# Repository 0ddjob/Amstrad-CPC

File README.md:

# Amstrad CPC
Amstrad CPC related projects.

## [Typer-Inner-Checker](/Typer-Inner-Checker)
A simple HTML/web page to aid typing in Locomotive BASIC program listings on a modern computer.  It doesn't run the program, that's for a proper emulator.<br>

This HTML page will:
- Check each line as you type it in
- Colourise/capitalise keywords
- Highlights missing GOTO/GOSUB targets
- Save/load BAS file for resuming where you left off

## [CPC PLUS Floppy Adaptor](/CPC_Plus_Floppy_Adaptor)
An idea to convert the 6128 PLUS model's Centronics floppy connector to a more standard 26-way or 34-way pin header to connect a drive via a ribbon cable.<br>

### Status
21-May-2026: test boards being fabricated

## [Dual ROM Adaptor for CPC464](/CPC464_Dual_ROM)
An idea for a no-cut adaptor board to allow two 32KB ROM images to be installed/switchable on a 64KB EPROM.  This means you could have the original 464 firmware/BASIC 1.0 and 664 (or 6128) firmware/BASIC 1.1 easily switchable.  Alternatively you could install a diagnostic ROM in one of the 32KB banks.<br>

Of course you would need to de-solder the original ROM and install this, but you wouldn't need to worry about cutting the PCB and wiring up pin 1, and you can just reinstall the original ROM.<br>

### Status
21-May-2026: test boards being fabricated

## [Amstrad CPC Troubleshooting Keyboard](/Amstrad_CPC_Keyboard)
Started off as a quick'n'dirty keyboard for my 2nd CPC664 motherboard that's missing the top case/keyboard, then morphed to a generic CPC keyboard that could be used for troubleshooting naked motherboards.<br>

### Status
25-Jul-2025: work in progress<br>

## [Easy Add on Projects for Amstrad CPC](/Easy-Add-on-Projects-for-Amstrad-CPC)
Trying out hardware projects from the book.

## [VGA4CPC](/VGA4CPC_Brett)
A modification of [grzegorz_gr's original design](https://github.com/grzegorz-gr/vga4cpc) to use with [WacKEDmaN's enhanced firmware](https://github.com/WacKEDmaN/VGA4CPC-Enhanced).<br>

- Rev. A: original re-design of grzegorz-gr's original, adding 6-pin & 8-pin DIN input sockets plus 3.5mm audio pass-through & 2.1mm DC power input
- Rev. B: added buffer on VGA output as suggest by [WacKEDmaN](https://github.com/WacKEDmaN/VGA4CPC-Enhanced#optional-hardware-mods), pass-through for B&W LUM signal, extra push button & breakout of spare GPIOs
- Rev. C: removed CPC PLUS 8-pin DIN to reduce board size (<100x100mm) for cheaper fabrication, adjusted resistor values
- Rev. D: added the CPC PLUS 8-pin DIN back in plus 3.5mm stereo audio output, remaining under 100x100mm
- Rev. E: swapped TLV3212 (SOIC-8) comparator for TLV3232 (SSOP-8) as it's faster
- Rev. F: moved the [comparator to its own daughterboard](/Amstrad-CPC/VGA4CPC_Brett/Comparator_Board) (simplifies circuit routing), switched to 5V logic (Pico 2 required), also switching the 74LVC245 (SMD) to 74HCT245 (THT)

### Status
22-May-2025: Rev. C pending fab & testing

## [CPC DIN to VGA](/CPC_DIN-to-VGA)
This is just a very simple connector converter - convert the CPC/CPC PLUS DIN to VGA, with also an RCA for the B&W LUM signal and 3.5mm stereo socket for the PLUSs' audio output.<br>

The idea is that you can then more easily plug it into a device with a VGA socket (like GBS8200) for actual signal conversion.<br>

## [Laserwarp](/Laserwarp)
Laserwarp was the first game, with Map Rally, that we got with our green screen Amstrad CPC464 so I have fond memories.<br>

I thought it might be interesting to try out Claude to disassemble and delve into how the game works.<br>

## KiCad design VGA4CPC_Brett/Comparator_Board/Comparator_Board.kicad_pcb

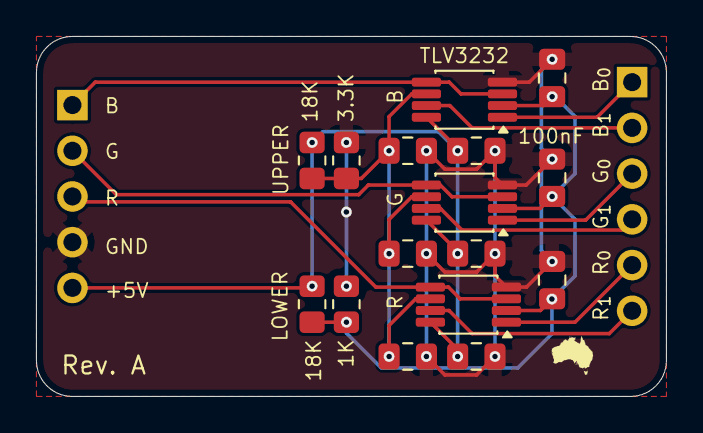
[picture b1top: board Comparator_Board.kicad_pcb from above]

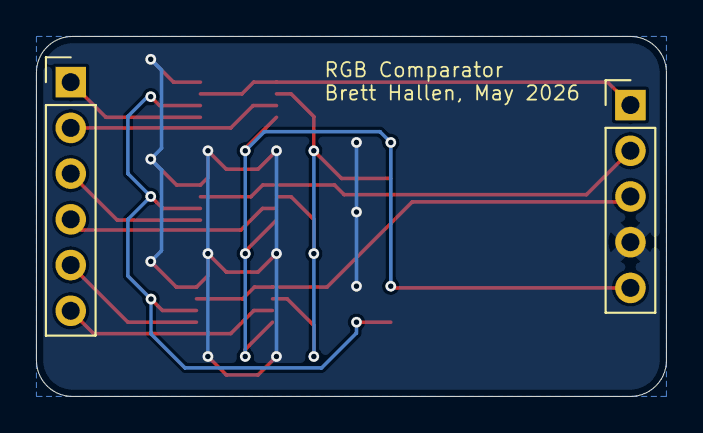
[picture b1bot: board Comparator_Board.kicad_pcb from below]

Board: 2 copper layers, 35.0 x 20.0 mm, 18 parts (2 on the bottom side), 13 nets.

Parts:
C1, C2, C3, C4, C5, C6, C7, C8, C9: 100nF; C_0805_2012Metric_Pad1.18x1.45mm_HandSolder
J1: INPUT; PinHeader_1x05_P2.54mm_Vertical
J2: OUTPUT; PinHeader_1x06_P2.54mm_Vertical
R1, R3: 18K; R_0805_2012Metric_Pad1.20x1.40mm_HandSolder
R2: 3.3K; R_0805_2012Metric_Pad1.20x1.40mm_HandSolder
R4: 1K; R_0805_2012Metric_Pad1.20x1.40mm_HandSolder
U1, U2, U3: TLV3232; VSSOP-8_3x3mm_P0.65mm

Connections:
+5V: C6.1, C8.1, C9.1, J1.5, R1.2, R3.2, U1.8 (VCC), U2.8 (VCC), U3.8 (VCC)
/B_{0}: J2.1, U1.1 (1OUT)
/B_{1}: J2.2, U1.7 (2OUT)
/CPC_B: J1.1, U1.3 (1IN+), U1.5 (2IN+)
/CPC_G: J1.2, U3.3 (1IN+), U3.5 (2IN+)
/CPC_R: J1.3, U2.3 (1IN+), U2.5 (2IN+)
/G_{0}: J2.3, U3.1 (1OUT)
/G_{1}: J2.4, U3.7 (2OUT)
/LOWER: C1.1, C2.1, C3.1, R3.1, R4.1, U1.2 (1IN-), U2.2 (1IN-), U3.2 (1IN-)
/R_{0}: J2.5, U2.1 (1OUT)
/R_{1}: J2.6, U2.7 (2OUT)
/UPPER: C4.1, C5.1, C7.1, R1.1, R2.2, U1.6 (2IN-), U2.6 (2IN-), U3.6 (2IN-)
GND: C1.2, C2.2, C3.2, C4.2, C5.2, C6.2, C7.2, C8.2, C9.2, J1.4, R2.1, R4.2, U1.4 (GND), U2.4 (GND), U3.4 (GND)

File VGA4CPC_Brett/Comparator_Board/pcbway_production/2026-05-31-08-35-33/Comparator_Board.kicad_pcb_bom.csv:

Designator,Quantity,Value,Footprint,Package,MPN,DNP,Mount_Type,Description,Height,Mouser Part Number,Mouser Price/Stock,Manufacturer_Name
"C1, C2, C3, C4, C5, C6, C7, C8, C9",9,100nF,C_0805_2012Metric_Pad1.18x1.45mm_HandSolder,,,,smt,,,,,
J1,1,INPUT,PinHeader_1x05_P2.54mm_Vertical,,,,tht,"Generic connector, single row, 01x05, script generated (kicad-library-utils/schlib/autogen/connector/)",,,,
J2,1,OUTPUT,PinHeader_1x06_P2.54mm_Vertical,,,,tht,"Generic connector, single row, 01x06, script generated (kicad-library-utils/schlib/autogen/connector/)",,,,
R1,1,17KΩ,R_0805_2012Metric_Pad1.20x1.40mm_HandSolder,,,,smt,"Resistor, small symbol",,,,
R2,1,3KΩ,R_0805_2012Metric_Pad1.20x1.40mm_HandSolder,,,,smt,"Resistor, small symbol",,,,
R3,1,19KΩ,R_0805_2012Metric_Pad1.20x1.40mm_HandSolder,,,,smt,"Resistor, small symbol",,,,
R4,1,1KΩ,R_0805_2012Metric_Pad1.20x1.40mm_HandSolder,,,,smt,"Resistor, small symbol",,,,
"U1, U2, U3",3,TLV3232,VSSOP-8_3x3mm_P0.65mm,,TLV3202AID,,smt,"Dual, 40ns, microPower, Rail-to-Rail input  Comparator with Push-pull outputs",1.75,595-TLV3202AID,https://www.mouser.co.uk/ProductDetail/Texas-Instruments/TLV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,Texas Instruments

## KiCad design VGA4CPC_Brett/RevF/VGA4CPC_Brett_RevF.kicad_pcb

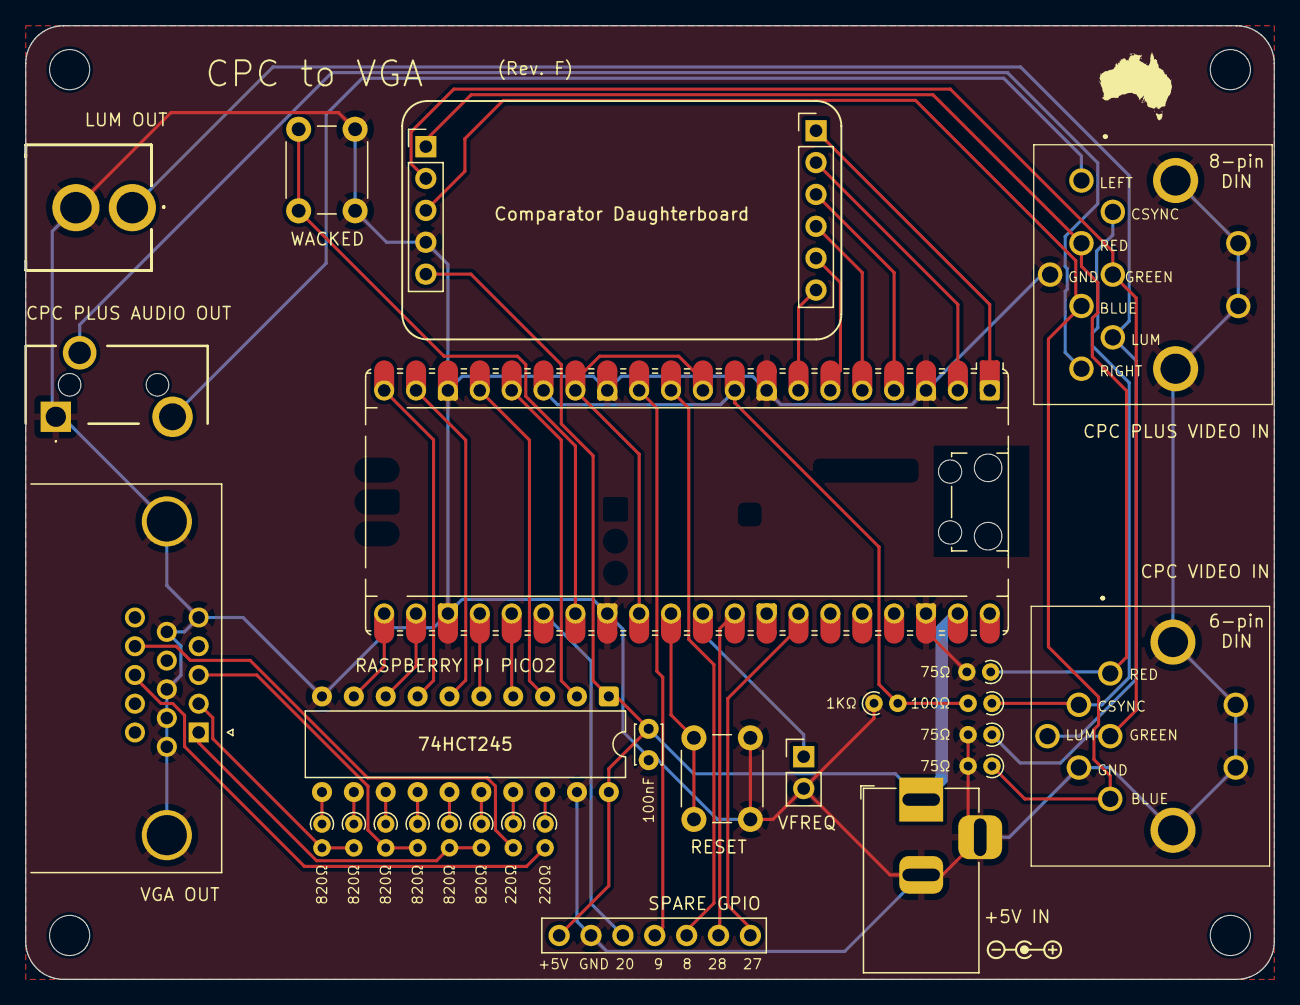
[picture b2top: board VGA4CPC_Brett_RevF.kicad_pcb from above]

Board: 2 copper layers, 99.5 x 76.0 mm, 31 parts (0 on the bottom side), 46 nets.

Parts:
C1: 100nF; C_Disc_D3.0mm_W2.0mm_P2.50mm
H1, H2, H3, H4: MountingHole; MountingHole_3.2mm_M3
J1: CPC VIDEO IN; SDF80J
J2: LUM OUT; 1560099E
J3: +5V IN; BarrelJack_Horizontal
J4: VFREQ; PinHeader_1x02_P2.54mm_Vertical
J5: SPARE GPIO; PinHeader_1x07_P2.54mm_Vertical
J6: VGA OUT; DSUB-15-HD_Socket_Horizontal_P2.29x2.54mm_EdgePinOffset8.35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
J7: CPC PLUS VIDEO IN; SDF80J
J8: CPC PLUS AUDIO OUT; SJ335083ATR
R1, R2, R3: 75Ω; R_Axial_DIN0204_L3.6mm_D1.6mm_P1.90mm_Vertical
R4: 100Ω; R_Axial_DIN0204_L3.6mm_D1.6mm_P1.90mm_Vertical
R5: 1KΩ; R_Axial_DIN0204_L3.6mm_D1.6mm_P1.90mm_Vertical
R6, R7, R8, R9, R10, R11: 820Ω; R_Axial_DIN0204_L3.6mm_D1.6mm_P1.90mm_Vertical
R12, R13: 220Ω; R_Axial_DIN0204_L3.6mm_D1.6mm_P1.90mm_Vertical
SW1: RESET; SW_PUSH_6mm
SW2: WACKED; SW_PUSH_6mm
U1: RASPBERRY PI PICO2; RaspberryPi_Pico_Common_Unspecified
U2: 74HCT245; DIP-20_W7.62mm
U6: Comparator Daughterboard

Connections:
+5V: C1.2, J3.1, J5.7, U1.39 (VSYS), U2.1 (A->B), U2.20 (VCC), U6.11 (+5V)
/B_{0}: U1.1 (GPIO0), U6.1 (B_{0})
/B_{1}: U1.2 (GPIO1), U6.2 (B_{1})
/CPC_AUDIO_L: J7.6, J8.T
/CPC_AUDIO_R: J7.7, J8.R
/CPC_B: J1.3, J7.5, R1.1, U6.9 (CPC_{BLUE})
/CPC_CSYNC: J1.4, J7.1, R4.1
/CPC_G: J1.2, J7.2, R2.1, U6.8 (CPC_{GREEN})
/CPC_LUM: J1.6, J2.1 (In), J7.3
/CPC_R: J1.1, J7.4, R3.1, U6.7 (CPC_{RED})
/CSYNC: R4.2, R5.2, U1.9 (GPIO6), U1.15 (GPIO11)
/GPIO8: J5.3, U1.11 (GPIO8)
/GPIO9: J5.4, U1.12 (GPIO9)
/GPIO20: J5.5, U1.26 (GPIO20)
/GPIO27: J5.2, U1.32 (GPIO27_ADC1)
/GPIO28: J5.1, U1.34 (GPIO28_ADC2)
/G_{0}: U1.4 (GPIO2), U6.3 (G_{0})
/G_{1}: U1.5 (GPIO3), U6.4 (G_{1})
/INT_VSYNC: U1.10 (GPIO7), U1.14 (GPIO10), U1.29 (GPIO22)
/R_{0}: U1.6 (GPIO4), U6.5 (R_{0})
/R_{1}: U1.7 (GPIO5), U6.6 (R_{1})
/VGA_B: J6.3, R8.2, R9.2
/VGA_B_{0}: U1.19 (GPIO14), U2.6 (A4)
/VGA_B_{1}: U1.20 (GPIO15), U2.7 (A5)
/VGA_G: J6.2, R6.2, R7.2
/VGA_G_{0}: U1.21 (GPIO16), U2.9 (A7)
/VGA_G_{1}: U1.22 (GPIO17), U2.8 (A6)
/VGA_HSYNC: U1.16 (GPIO12), U2.2 (A0)
/VGA_HSYNC_{B}: J6.13, R12.2
/VGA_R: J6.1, R10.2, R11.2
/VGA_R_{0}: U1.24 (GPIO18), U2.5 (A3)
/VGA_R_{1}: U1.25 (GPIO19), U2.4 (A2)
/VGA_VSYNC: U1.17 (GPIO13), U2.3 (A1)
/VGA_VSYNC_{B}: J6.14, R13.2
GND: C1.1, J1.5, J2.2 (Ext), J3.2, J4.2, J5.6, J6.0, J6.5, J6.6, J6.7, J6.8, J6.10, J7.8, J8.S, R1.2, R2.2, R3.2, R5.1, SW1.1, SW2.2, U1.3 (GND), U1.8 (GND), U1.13 (GND), U1.18 (GND), U1.23 (GND), U1.28 (GND), U1.38 (GND), U2.10 (GND), U2.19 (CE), U6.10 (GND)
unnamed: J4.1, U1.31 (GPIO26_ADC0)
unnamed: SW2.1, U1.27 (GPIO21)
unnamed: SW1.2, U1.30 (RUN)
unnamed: R12.1, U2.18 (B0)
unnamed: R13.1, U2.17 (B1)
unnamed: R10.1, U2.16 (B2)
unnamed: R11.1, U2.15 (B3)
unnamed: R8.1, U2.14 (B4)
unnamed: R9.1, U2.13 (B5)
unnamed: R6.1, U2.12 (B6)
unnamed: R7.1, U2.11 (B7)

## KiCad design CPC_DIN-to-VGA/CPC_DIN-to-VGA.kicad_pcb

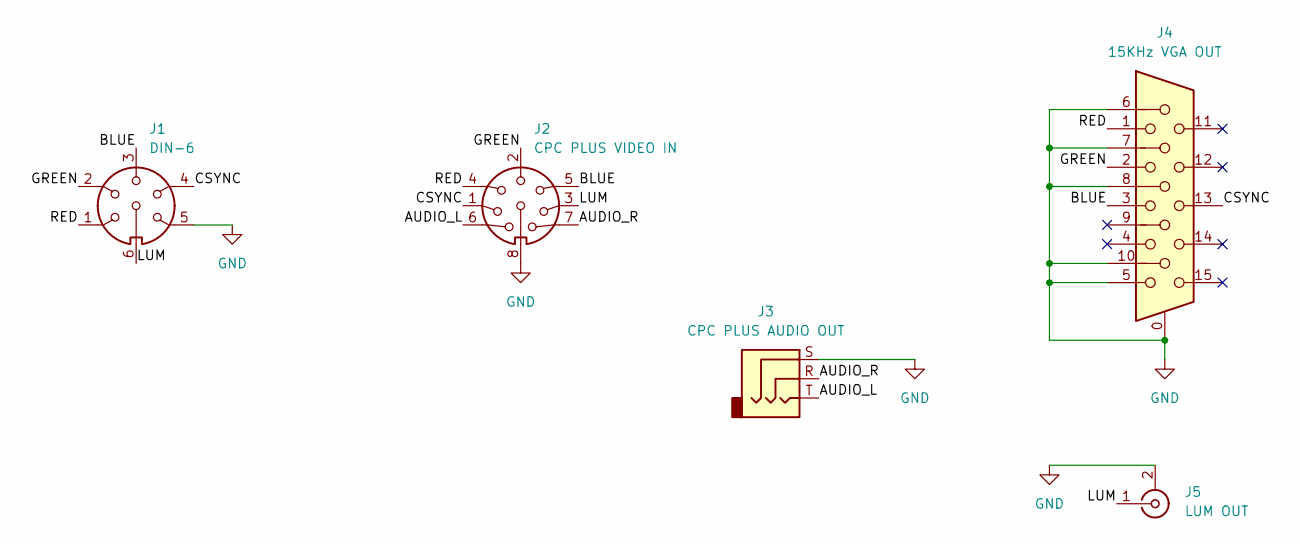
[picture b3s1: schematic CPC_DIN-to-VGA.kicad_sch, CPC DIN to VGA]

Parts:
J1: DIN-6; SDF80J
J2: CPC PLUS VIDEO IN; SDF80J
J3: CPC PLUS AUDIO OUT; SJ335083ATR
J4: 15KHz VGA OUT; DSUB-15-HD_Socket_Horizontal_P2.29x2.54mm_EdgePinOffset8.35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
J5: LUM OUT; 1560099E

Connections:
/AUDIO_L: J2.6, J3.T
/AUDIO_R: J2.7, J3.R
/BLUE: J1.3, J2.5, J4.3
/CSYNC: J1.4, J2.1, J4.13
/GREEN: J1.2, J2.2, J4.2
/LUM: J1.6, J2.3, J5.1 (In)
/RED: J1.1, J2.4, J4.1
GND: J1.5, J2.8, J3.S, J4.0, J4.5, J4.6, J4.7, J4.8, J4.10, J5.2 (Ext)

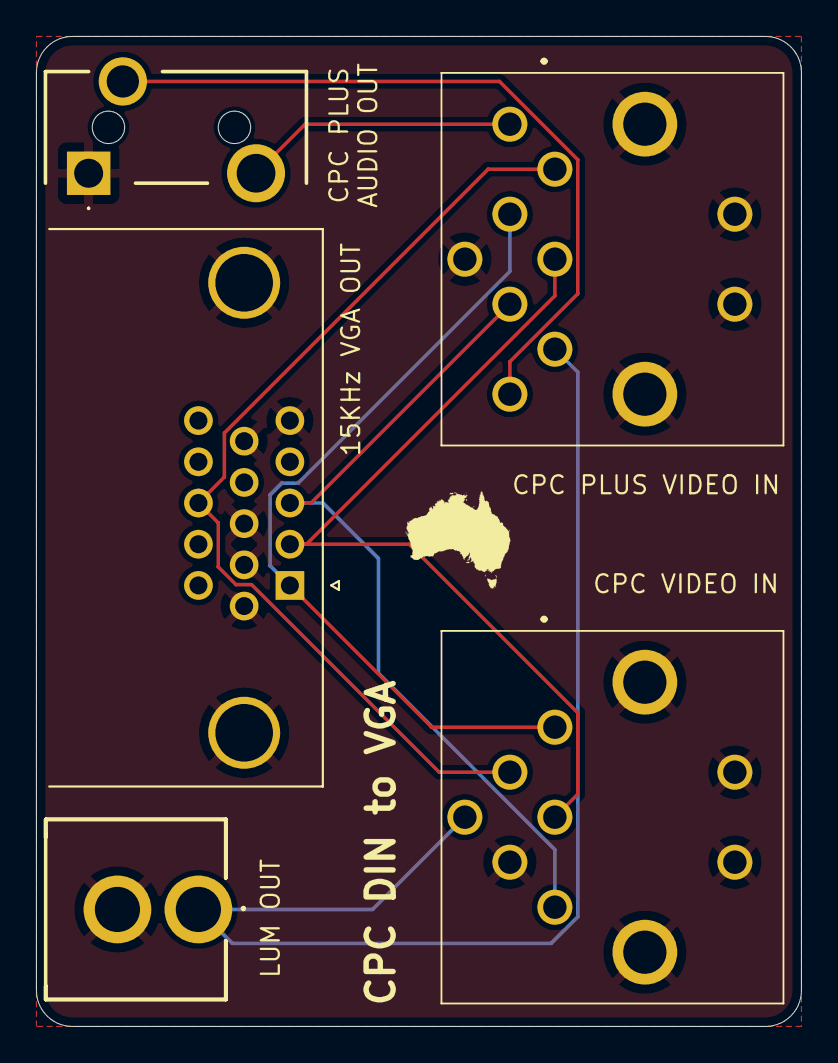
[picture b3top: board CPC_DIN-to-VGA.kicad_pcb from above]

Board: 2 copper layers, 42.5 x 55.0 mm, 5 parts (0 on the bottom side), 8 nets.

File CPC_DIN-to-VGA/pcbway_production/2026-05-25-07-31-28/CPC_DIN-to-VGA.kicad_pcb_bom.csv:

Designator,Quantity,Value,Footprint,Package,MPN,DNP,Mount_Type,Description
J1,1,DIN-6,SDF80J,,,,tht,6-pin DIN connector
J2,1,CPC PLUS VIDEO IN,SDF80J,,,,tht,8-pin DIN connector
J3,1,CPC PLUS AUDIO OUT,SJ335083ATR,,,,tht,"Audio Jack, 3 Poles (Stereo / TRS)"
J4,1,VGA OUT,DSUB-15-HD_Socket_Horizontal_P2.29x2.54mm_EdgePinOffset8.35mm_Housed_MountingHolesOffset10.89mm,,,,tht,"15-pin D-SUB connector, socket (female), High density (3 columns), Triple Row, Generic, VGA-connector, Mounting Hole"
J5,1,LUM OUT,1560099E,,,,tht,"coaxial connector (BNC, SMA, SMB, SMC, Cinch/RCA, LEMO, ...)"

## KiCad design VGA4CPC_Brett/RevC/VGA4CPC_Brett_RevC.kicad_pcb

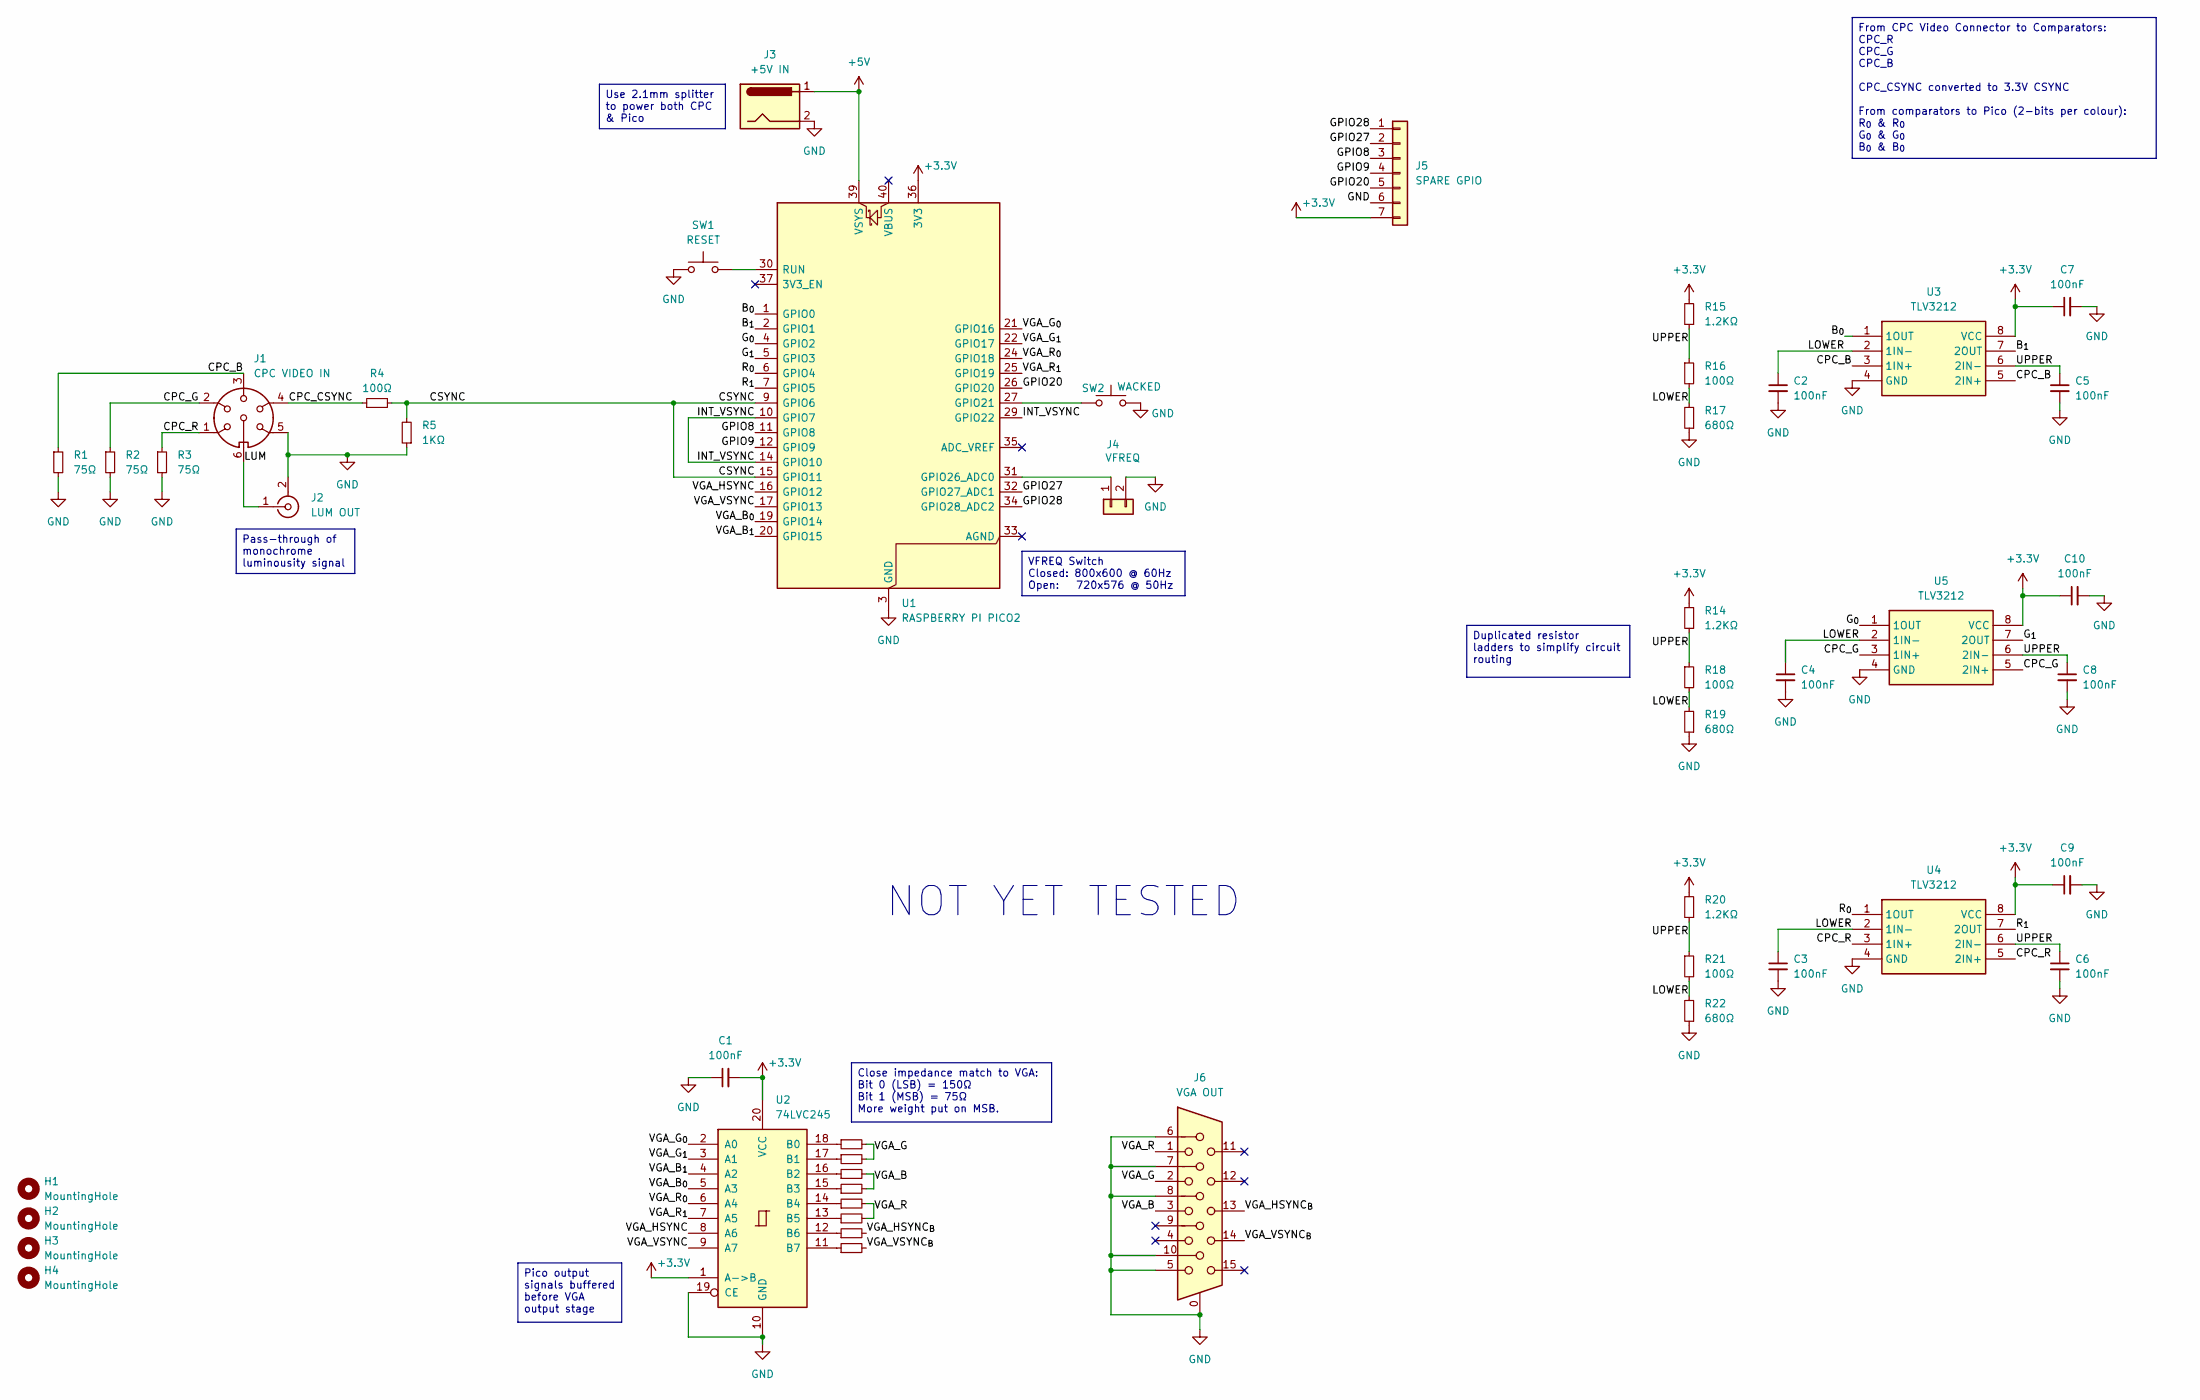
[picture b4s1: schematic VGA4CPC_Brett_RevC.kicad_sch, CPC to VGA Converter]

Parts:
C1, C2, C3, C4, C5, C6, C7, C8, C9, C10: 100nF; C_Disc_D3.0mm_W2.0mm_P2.50mm
H1, H2, H3, H4: MountingHole; MountingHole_3.2mm_M3
J1: CPC VIDEO IN; SDF80J
J2: LUM OUT; 1560099E
J3: +5V IN; BarrelJack_Horizontal
J4: VFREQ; PinHeader_1x02_P2.54mm_Vertical
J5: SPARE GPIO; PinHeader_1x07_P2.54mm_Vertical
J6: VGA OUT; DSUB-15-HD_Socket_Horizontal_P2.29x2.54mm_EdgePinOffset8.35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
R1, R2, R3, R7, R8, R11: 75Ω; R_Axial_DIN0204_L3.6mm_D1.6mm_P1.90mm_Vertical
R4, R16, R18, R21: 100Ω; R_Axial_DIN0204_L3.6mm_D1.6mm_P1.90mm_Vertical
R5: 1KΩ; R_Axial_DIN0204_L3.6mm_D1.6mm_P1.90mm_Vertical
R6, R9, R10: 150Ω; R_Axial_DIN0204_L3.6mm_D1.6mm_P1.90mm_Vertical
R12, R13: 220Ω; R_Axial_DIN0204_L3.6mm_D1.6mm_P1.90mm_Vertical
R14, R15, R20: 1.2KΩ; R_Axial_DIN0204_L3.6mm_D1.6mm_P1.90mm_Vertical
R17, R19, R22: 680Ω; R_Axial_DIN0204_L3.6mm_D1.6mm_P1.90mm_Vertical
SW1: RESET; SW_PUSH_6mm
SW2: WACKED; SW_PUSH_6mm
U1: RASPBERRY PI PICO2; RaspberryPi_Pico_Common_Unspecified
U2: 74LVC245; SOIC-20W_7.5x12.8mm_P1.27mm
U3, U4, U5: TLV3212; SOIC-8_3.9x4.9mm_P1.27mm; Mouser Part Number 595-TLV3202AID

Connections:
+3.3V: C1.2, C7.1, C9.1, C10.1, J5.7, R14.2, R15.2, R20.2, U1.36 (3V3), U2.1 (A->B), U2.20 (VCC), U3.8 (VCC), U4.8 (VCC), U5.8 (VCC)
+5V: J3.1, U1.39 (VSYS)
/B_{0}: U1.1 (GPIO0), U3.1 (1OUT)
/B_{1}: U1.2 (GPIO1), U3.7 (2OUT)
/CPC_B: J1.3, R1.1, U3.3 (1IN+), U3.5 (2IN+)
/CPC_CSYNC: J1.4, R4.1
/CPC_G: J1.2, R2.1, U5.3 (1IN+), U5.5 (2IN+)
/CPC_R: J1.1, R3.1, U4.3 (1IN+), U4.5 (2IN+)
/CSYNC: R4.2, R5.2, U1.9 (GPIO6), U1.15 (GPIO11)
/GPIO8: J5.3, U1.11 (GPIO8)
/GPIO9: J5.4, U1.12 (GPIO9)
/GPIO20: J5.5, U1.26 (GPIO20)
/GPIO27: J5.2, U1.32 (GPIO27_ADC1)
/GPIO28: J5.1, U1.34 (GPIO28_ADC2)
/G_{0}: U1.4 (GPIO2), U5.1 (1OUT)
/G_{1}: U1.5 (GPIO3), U5.7 (2OUT)
/INT_VSYNC: U1.10 (GPIO7), U1.14 (GPIO10), U1.29 (GPIO22)
/LOWER: C2.1, C3.1, C4.1, R16.2, R17.2, R18.2, R19.2, R21.2, R22.2, U3.2 (1IN-), U4.2 (1IN-), U5.2 (1IN-)
/LUM: J1.6, J2.1 (In)
/R_{0}: U1.6 (GPIO4), U4.1 (1OUT)
/R_{1}: U1.7 (GPIO5), U4.7 (2OUT)
/UPPER: C5.1, C6.1, C8.1, R14.1, R15.1, R16.1, R18.1, R20.1, R21.1, U3.6 (2IN-), U4.6 (2IN-), U5.6 (2IN-)
/VGA_B: J6.3, R8.2, R9.2
/VGA_B_{0}: U1.19 (GPIO14), U2.5 (A3)
/VGA_B_{1}: U1.20 (GPIO15), U2.4 (A2)
/VGA_G: J6.2, R6.2, R7.2
/VGA_G_{0}: U1.21 (GPIO16), U2.2 (A0)
/VGA_G_{1}: U1.22 (GPIO17), U2.3 (A1)
/VGA_HSYNC: U1.16 (GPIO12), U2.8 (A6)
/VGA_HSYNC_{B}: J6.13, R12.2
/VGA_R: J6.1, R10.2, R11.2
/VGA_R_{0}: U1.24 (GPIO18), U2.6 (A4)
/VGA_R_{1}: U1.25 (GPIO19), U2.7 (A5)
/VGA_VSYNC: U1.17 (GPIO13), U2.9 (A7)
/VGA_VSYNC_{B}: J6.14, R13.2
GND: C1.1, C2.2, C3.2, C4.2, C5.2, C6.2, C7.2, C8.2, C9.2, C10.2, J1.5, J2.2 (Ext), J3.2, J4.2, J5.6, J6.0, J6.5, J6.6, J6.7, J6.8, J6.10, R1.2, R2.2, R3.2, R5.1, R17.1, R19.1, R22.1, SW1.1, SW2.2, U1.3 (GND), U1.8 (GND), U1.13 (GND), U1.18 (GND), U1.23 (GND), U1.28 (GND), U1.38 (GND), U2.10 (GND), U2.19 (CE), U3.4 (GND), U4.4 (GND), U5.4 (GND)
unnamed: J4.1, U1.31 (GPIO26_ADC0)
unnamed: SW2.1, U1.27 (GPIO21)
unnamed: SW1.2, U1.30 (RUN)
unnamed: R6.1, U2.18 (B0)
unnamed: R7.1, U2.17 (B1)
unnamed: R8.1, U2.16 (B2)
unnamed: R9.1, U2.15 (B3)
unnamed: R10.1, U2.14 (B4)
unnamed: R11.1, U2.13 (B5)
unnamed: R12.1, U2.12 (B6)
unnamed: R13.1, U2.11 (B7)

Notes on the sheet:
NOT YET TESTED
From CPC Video Connector to Comparators: CPC_R CPC_G CPC_B CPC_CSYNC converted to 3.3V CSYNC From comparators to Pico (2-bits per colour): R_{0} & R_{0} G_{0} & G_{0} B_{0} & B_{0}
Use 2.1mm splitter to power both CPC & Pico
VFREQ Switch Closed: 800x600 @ 60Hz Open: 720x576 @ 50Hz
Pass-through of monochrome luminousity signal
Pico output signals buffered before VGA output stage
Duplicated resistor ladders to simplify circuit routing
Close impedance match to VGA: Bit 0 (LSB) = 150Ω Bit 1 (MSB) = 75Ω More weight put on MSB.

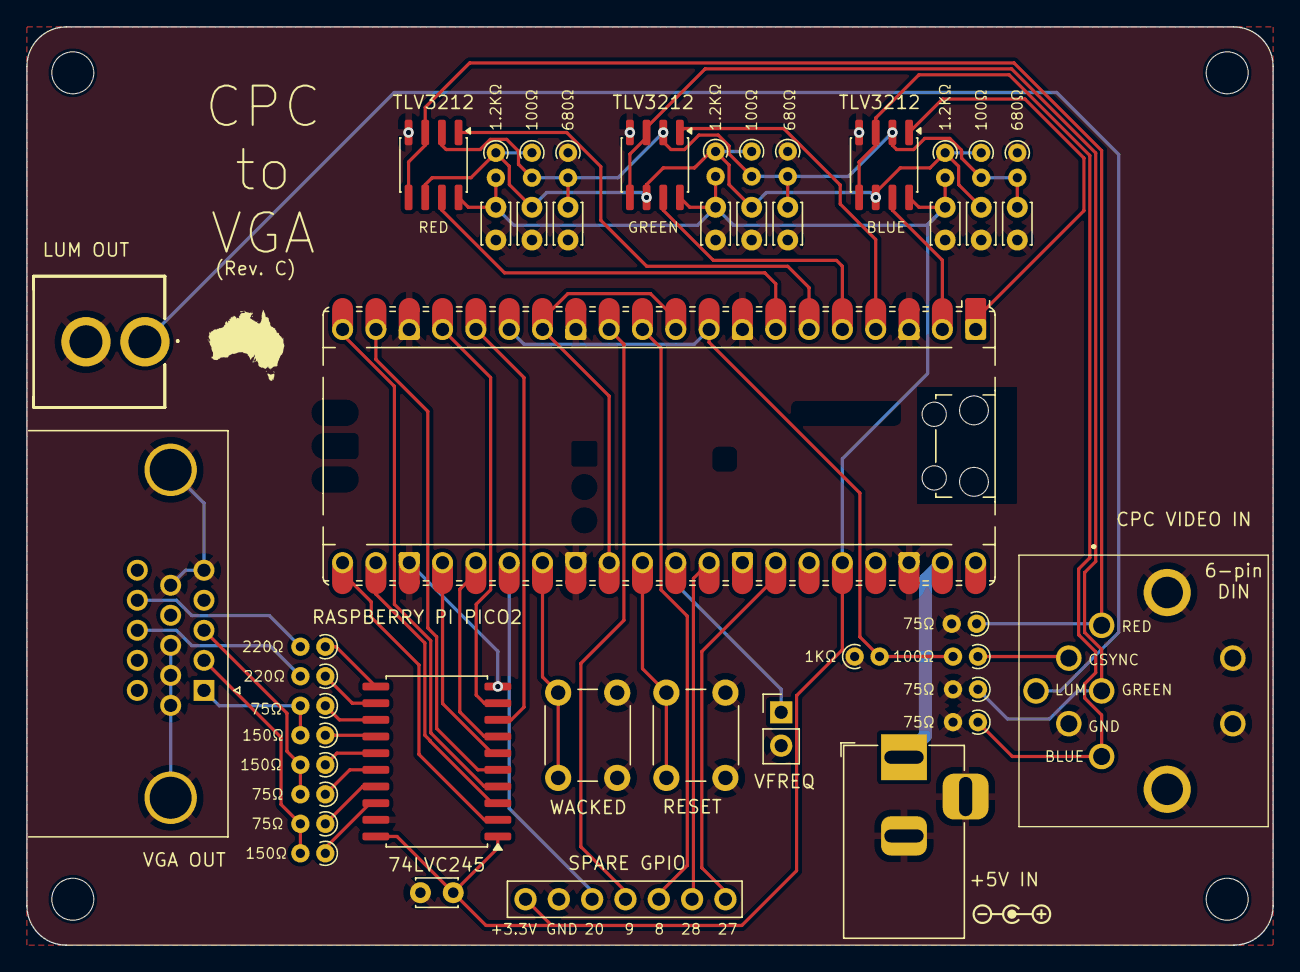
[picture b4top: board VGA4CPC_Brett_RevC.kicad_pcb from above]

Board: 2 copper layers, 95.0 x 70.0 mm, 49 parts (0 on the bottom side), 47 nets.

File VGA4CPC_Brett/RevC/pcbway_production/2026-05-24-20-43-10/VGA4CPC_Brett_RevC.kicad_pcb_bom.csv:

Designator,Quantity,Value,Footprint,Package,MPN,DNP,Mount_Type,Description,Height,Mouser Part Number,Mouser Price/Stock,Manufacturer_Name
"C1, C10, C2, C3, C4, C5, C6, C7, C8, C9",10,100nF,C_Disc_D3.0mm_W2.0mm_P2.50mm,,,,tht,,,,,
"H1, H2, H3, H4",4,MountingHole,MountingHole_3.2mm_M3,,,,tht,,,,,
J1,1,CPC VIDEO IN,SDF80J,,,,tht,Same Sky SDF-60J 6-pin DIN Socket,,,,
J2,1,LUM OUT,1560099E,,,,tht,"coaxial connector (BNC, SMA, SMB, SMC, Cinch/RCA, LEMO, ...)",,,,
J3,1,+5V IN,BarrelJack_Horizontal,,,,tht,DC Barrel Jack,,,,
J4,1,VFREQ,PinHeader_1x02_P2.54mm_Vertical,,,,tht,"Generic connector, single row, 01x02, script generated (kicad-library-utils/schlib/autogen/connector/)",,,,
J5,1,SPARE GPIO,PinHeader_1x06_P2.54mm_Vertical,,,,tht,"Generic connector, single row, 01x06, script generated (kicad-library-utils/schlib/autogen/connector/)",,,,
J6,1,VGA OUT,DSUB-15-HD_Socket_Horizontal_P2.29x2.54mm_EdgePinOffset8.35mm_Housed_MountingHolesOffset10.89mm,,,,tht,"15-pin D-SUB connector, socket (female), High density (3 columns), Triple Row, Generic, VGA-connector, Mounting Hole",,,,
"R1, R11, R2, R3, R7, R8",6,75Ω,R_Axial_DIN0204_L3.6mm_D1.6mm_P1.90mm_Vertical,,,,tht,"Resistor, small symbol",,,,
"R10, R6, R9",3,150Ω,R_Axial_DIN0204_L3.6mm_D1.6mm_P1.90mm_Vertical,,,,tht,"Resistor, small symbol",,,,
"R12, R13",2,220Ω,R_Axial_DIN0204_L3.6mm_D1.6mm_P1.90mm_Vertical,,,,tht,"Resistor, small symbol",,,,
"R14, R15, R20",3,1.2KΩ,R_Axial_DIN0204_L3.6mm_D1.6mm_P1.90mm_Vertical,,,,tht,"Resistor, small symbol",,,,
"R16, R18, R21, R4",4,100Ω,R_Axial_DIN0204_L3.6mm_D1.6mm_P1.90mm_Vertical,,,,tht,"Resistor, small symbol",,,,
"R17, R19, R22",3,680Ω,R_Axial_DIN0204_L3.6mm_D1.6mm_P1.90mm_Vertical,,,,tht,"Resistor, small symbol",,,,
R5,1,1KΩ,R_Axial_DIN0204_L3.6mm_D1.6mm_P1.90mm_Vertical,,,,tht,"Resistor, small symbol",,,,
SW1,1,RESET,SW_PUSH_6mm,,,,tht,"Push button switch, generic, two pins",,,,
SW2,1,WACKED,SW_PUSH_6mm,,,,tht,"Push button switch, generic, two pins",,,,
U1,1,RASPBERRY PI PICO2,RaspberryPi_Pico_Common_Unspecified,,,,tht,"Versatile and inexpensive microcontroller module powered by RP2040 dual-core Arm Cortex-M0+ processor up to 133 MHz, 264kB SRAM, 2MB QSPI flash; also supports Raspberry Pi Pico 2",,,,
U2,1,74LVC245,SOIC-20W_7.5x12.8mm_P1.27mm,,,,smt,"Octal BUS Transceivers, 3-State outputs",,,,
"U3, U4, U5",3,TLV3212,SOIC-8_3.9x4.9mm_P1.27mm,,TLV3202AID,,smt,"Dual, 40ns, microPower, Rail-to-Rail input  Comparator with Push-pull outputs",1.75,595-TLV3202AID,https://www.mouser.co.uk/ProductDetail/Texas-Instruments/TLV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,Texas Instruments

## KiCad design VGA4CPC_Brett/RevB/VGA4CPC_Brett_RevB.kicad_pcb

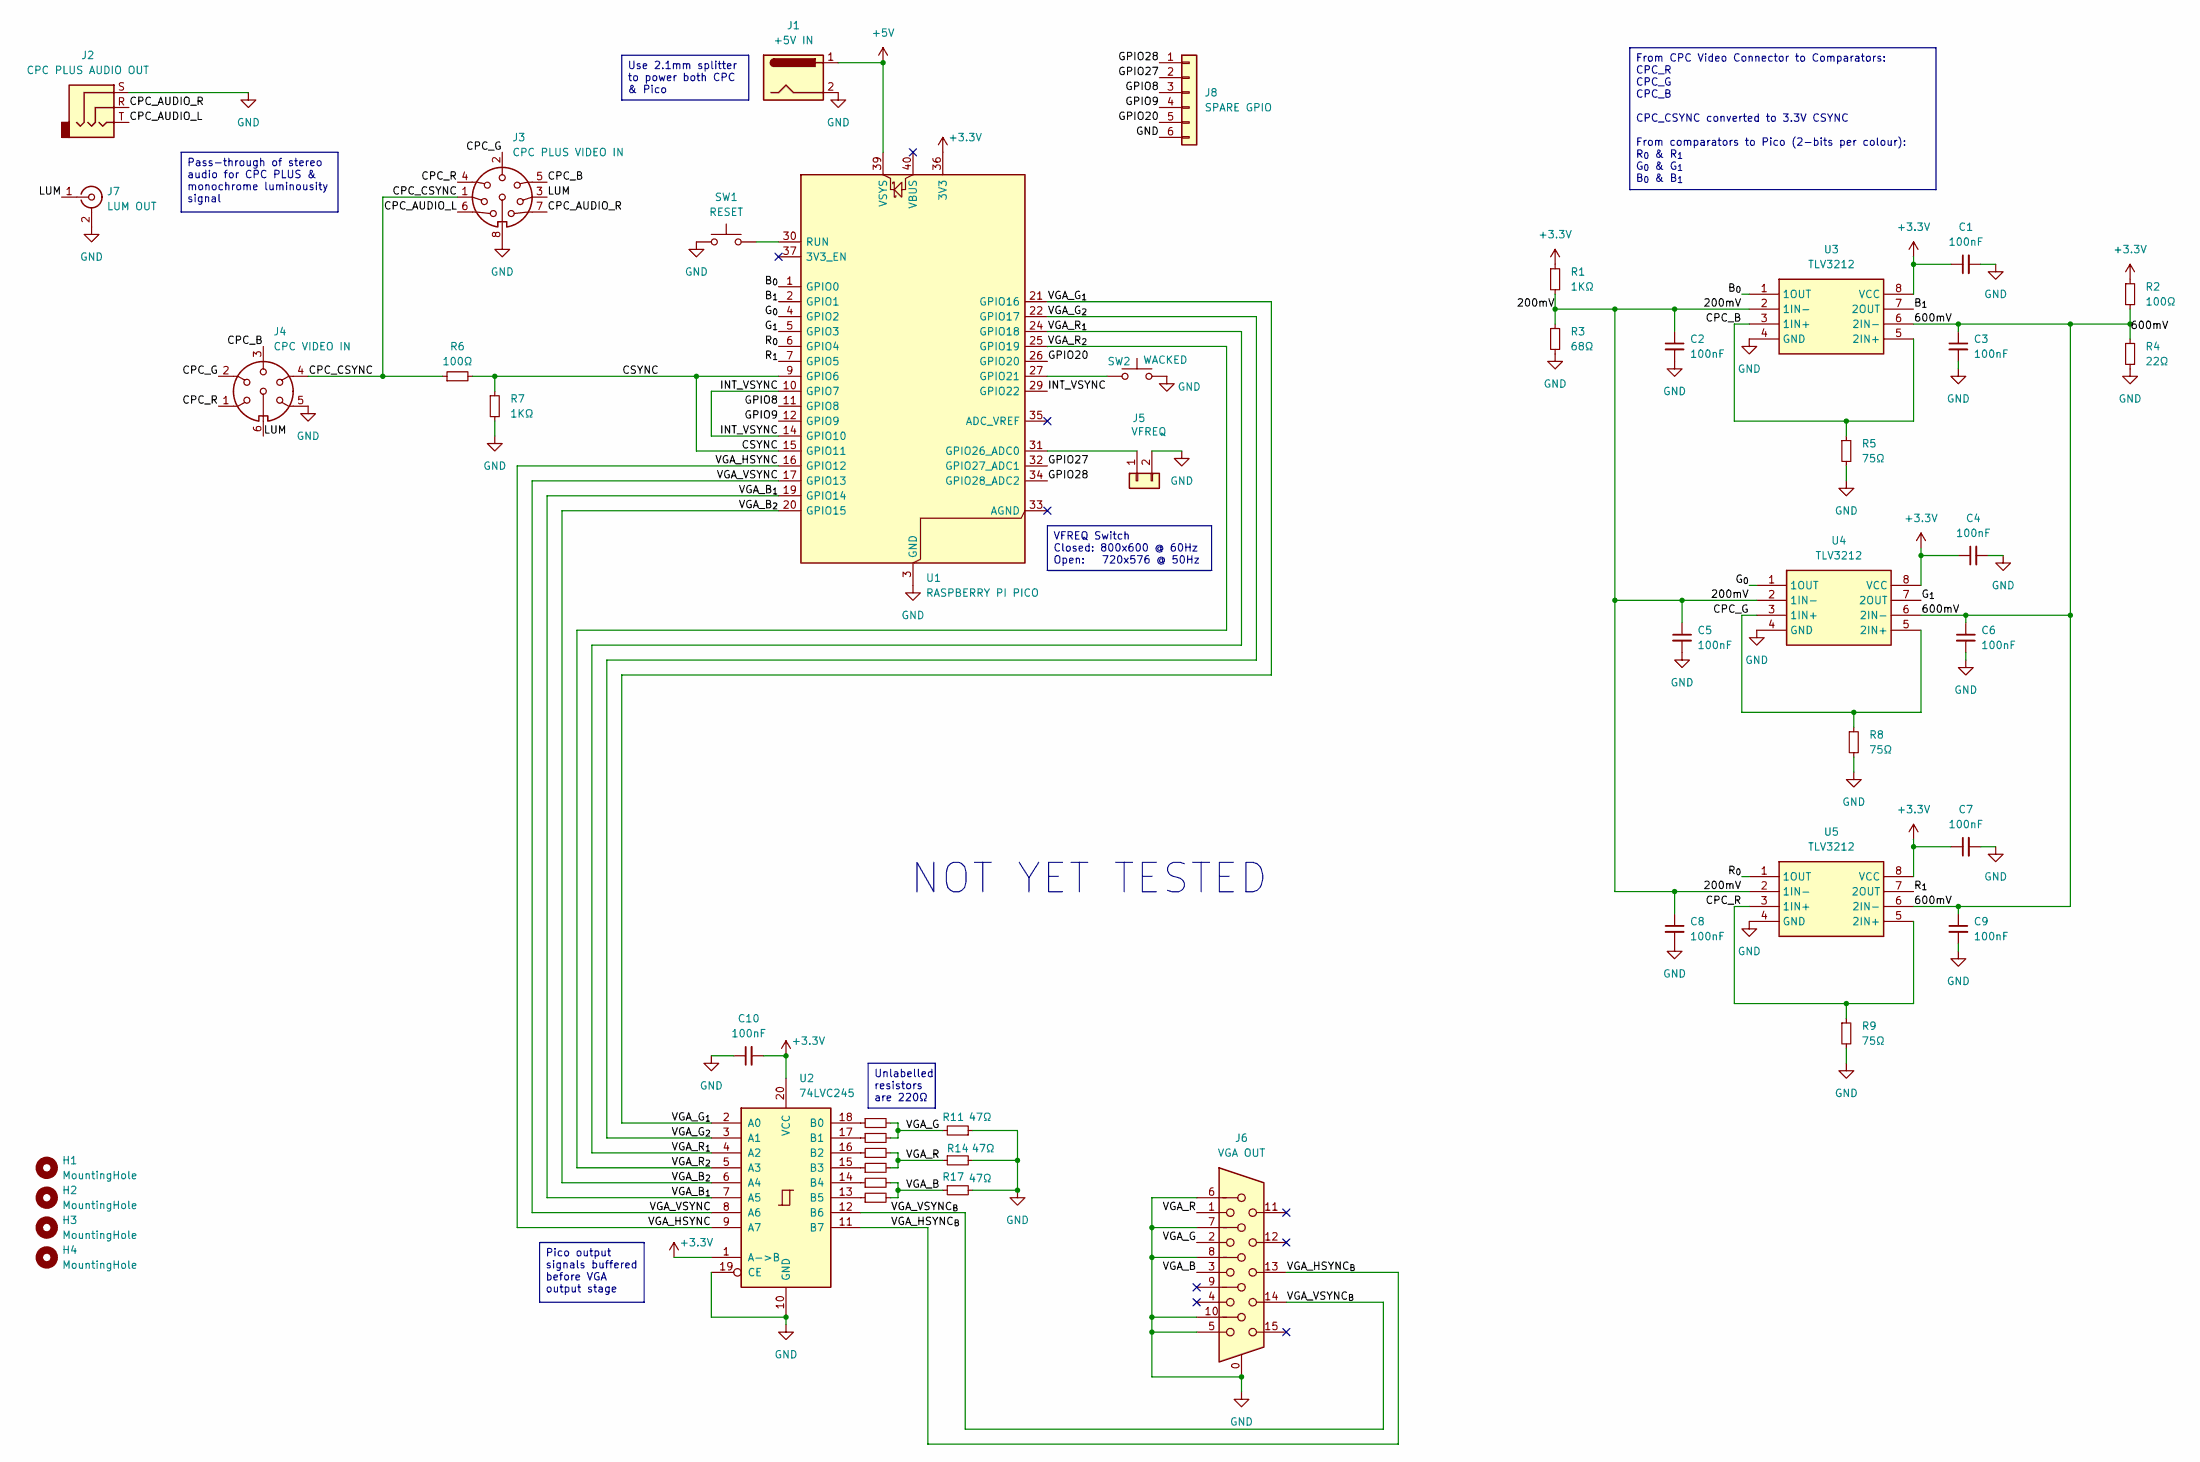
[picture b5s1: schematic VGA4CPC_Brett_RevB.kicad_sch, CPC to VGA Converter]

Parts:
C1, C2, C3, C4, C5, C6, C7, C8, C9, C10: 100nF; C_Disc_D3.4mm_W2.1mm_P2.50mm
H1, H2, H3, H4: MountingHole; MountingHole_3.2mm_M3
J1: +5V IN; BarrelJack_Horizontal
J2: CPC PLUS AUDIO OUT; SJ335083ATR
J3: CPC PLUS VIDEO IN; SDF80J
J4: CPC VIDEO IN; SDF80J
J5: VFREQ; PinHeader_1x02_P2.54mm_Vertical
J6: VGA OUT; DSUB-15-HD_Socket_Horizontal_P2.29x2.54mm_EdgePinOffset8.35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
J7: LUM OUT; 1560099E
J8: SPARE GPIO; PinHeader_1x06_P2.54mm_Vertical
R1, R7: 1KΩ; R_Axial_DIN0207_L6.3mm_D2.5mm_P7.62mm_Horizontal
R2, R6: 100Ω; R_Axial_DIN0207_L6.3mm_D2.5mm_P7.62mm_Horizontal
R3: 68Ω; R_Axial_DIN0207_L6.3mm_D2.5mm_P7.62mm_Horizontal
R4: 22Ω; R_Axial_DIN0207_L6.3mm_D2.5mm_P7.62mm_Horizontal
R5, R8, R9: 75Ω; R_Axial_DIN0207_L6.3mm_D2.5mm_P7.62mm_Horizontal
R10, R12, R13, R15, R16, R18: 220Ω; R_Axial_DIN0207_L6.3mm_D2.5mm_P7.62mm_Horizontal
R11, R14, R17: 47Ω; R_Axial_DIN0207_L6.3mm_D2.5mm_P7.62mm_Horizontal
SW1: RESET; SW_PUSH_6mm
SW2: WACKED; SW_PUSH_6mm
U1: RASPBERRY PI PICO; RaspberryPi_Pico_Common_Unspecified
U2: 74LVC245; SOIC-20W_7.5x12.8mm_P1.27mm
U3, U4, U5: TLV3212; SOIC-8_3.9x4.9mm_P1.27mm; Mouser Part Number 595-TLV3202AID

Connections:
+3.3V: C1.1, C4.1, C7.1, C10.2, R1.1, R2.1, U1.36 (3V3), U2.1 (A->B), U2.20 (VCC), U3.8 (VCC), U4.8 (VCC), U5.8 (VCC)
+5V: J1.1, U1.39 (VSYS)
/200mV: C2.1, C5.1, C8.1, R1.2, R3.1, U3.2 (1IN-), U4.2 (1IN-), U5.2 (1IN-)
/600mV: C3.1, C6.1, C9.1, R2.2, R4.1, U3.6 (2IN-), U4.6 (2IN-), U5.6 (2IN-)
/B_{0}: U1.1 (GPIO0), U3.1 (1OUT)
/B_{1}: U1.2 (GPIO1), U3.7 (2OUT)
/CPC_AUDIO_L: J2.T, J3.6
/CPC_AUDIO_R: J2.R, J3.7
/CPC_B: J3.5, J4.3, R5.1, U3.3 (1IN+), U3.5 (2IN+)
/CPC_CSYNC: J3.1, J4.4, R6.1
/CPC_G: J3.2, J4.2, R8.1, U4.3 (1IN+), U4.5 (2IN+)
/CPC_R: J3.4, J4.1, R9.1, U5.3 (1IN+), U5.5 (2IN+)
/CSYNC: R6.2, R7.1, U1.9 (GPIO6), U1.15 (GPIO11)
/GPIO8: J8.3, U1.11 (GPIO8)
/GPIO9: J8.4, U1.12 (GPIO9)
/GPIO20: J8.5, U1.26 (GPIO20)
/GPIO27: J8.2, U1.32 (GPIO27_ADC1)
/GPIO28: J8.1, U1.34 (GPIO28_ADC2)
/G_{0}: U1.4 (GPIO2), U4.1 (1OUT)
/G_{1}: U1.5 (GPIO3), U4.7 (2OUT)
/INT_VSYNC: U1.10 (GPIO7), U1.14 (GPIO10), U1.29 (GPIO22)
/LUM: J3.3, J4.6, J7.1 (In)
/R_{0}: U1.6 (GPIO4), U5.1 (1OUT)
/R_{1}: U1.7 (GPIO5), U5.7 (2OUT)
/VGA_B: J6.3, R16.2, R17.1, R18.2
/VGA_B_{1}: U1.19 (GPIO14), U2.7 (A5)
/VGA_B_{2}: U1.20 (GPIO15), U2.6 (A4)
/VGA_G: J6.2, R10.2, R11.2, R12.2
/VGA_G_{1}: U1.21 (GPIO16), U2.2 (A0)
/VGA_G_{2}: U1.22 (GPIO17), U2.3 (A1)
/VGA_HSYNC: U1.16 (GPIO12), U2.9 (A7)
/VGA_HSYNC_{B}: J6.13, U2.11 (B7)
/VGA_R: J6.1, R13.2, R14.1, R15.2
/VGA_R_{1}: U1.24 (GPIO18), U2.4 (A2)
/VGA_R_{2}: U1.25 (GPIO19), U2.5 (A3)
/VGA_VSYNC: U1.17 (GPIO13), U2.8 (A6)
/VGA_VSYNC_{B}: J6.14, U2.12 (B6)
GND: C1.2, C2.2, C3.2, C4.2, C5.2, C6.2, C7.2, C8.2, C9.2, C10.1, J1.2, J2.S, J3.8, J4.5, J5.2, J6.0, J6.5, J6.6, J6.7, J6.8, J6.10, J7.2 (Ext), J8.6, R3.2, R4.2, R5.2, R7.2, R8.2, R9.2, R11.1, R14.2, R17.2, SW1.1, SW2.2, U1.3 (GND), U1.8 (GND), U1.13 (GND), U1.18 (GND), U1.23 (GND), U1.28 (GND), U1.38 (GND), U2.10 (GND), U2.19 (CE), U3.4 (GND), U4.4 (GND), U5.4 (GND)
unnamed: J5.1, U1.31 (GPIO26_ADC0)
unnamed: SW2.1, U1.27 (GPIO21)
unnamed: SW1.2, U1.30 (RUN)
unnamed: R10.1, U2.18 (B0)
unnamed: R12.1, U2.17 (B1)
unnamed: R15.1, U2.16 (B2)
unnamed: R13.1, U2.15 (B3)
unnamed: R16.1, U2.14 (B4)
unnamed: R18.1, U2.13 (B5)

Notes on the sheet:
NOT YET TESTED
From CPC Video Connector to Comparators: CPC_R CPC_G CPC_B CPC_CSYNC converted to 3.3V CSYNC From comparators to Pico (2-bits per colour): R_{0} & R_{1} G_{0} & G_{1} B_{0} & B_{1}
Use 2.1mm splitter to power both CPC & Pico
Unlabelled resistors are 220Ω
VFREQ Switch Closed: 800x600 @ 60Hz Open: 720x576 @ 50Hz
Pass-through of stereo audio for CPC PLUS & monochrome luminousity signal
Pico output signals buffered before VGA output stage
